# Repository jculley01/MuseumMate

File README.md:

# MuseumMate

## Executive Summary

MuseumMate is an advanced indoor navigation and exhibit interaction system, designed to enrich museum visits. Upon entering a museum, visitors receive a handheld device, the TourTag, which detects Ultra-wideband (UWB) signals from beacons placed throughout the premises. This device transmits signal strengths to a server to pinpoint the visitor's location, facilitating precise navigation through a user-friendly web application. Additionally, RFID tags on exhibits interact with the TourTags, allowing visitors to automatically access rich multimedia content about the exhibits they are near, thus enhancing their educational and interactive experience in the museum. This system seamlessly integrates efficient navigation with engaging exhibit exploration, revolutionizing the traditional museum visit.

## Context

MuseumMate utilizes a blend of Ultra-Wideband (UWB) and Radio Frequency Identification (RFID) technologies to streamline visitor flow and provide immersive educational content. The system's core components include:

### UWB Beacons (ESP32 UWB DW3000)
 
These beacons are utilized with trilateration to provide location accuracy within 10 centimeters , facilitating real-time, room-by-room navigation and helping to manage museum traffic by suggesting alternative routes to avoid congestion.

### RFID Tags

Attached to each exhibit, these tags work in tandem with TourTags—portable user devices that visitors carry. When a visitor approaches an exhibit, the TourTag scans the RFID tag to fetch multimedia content related to the exhibit.

### Server Technology

- Node.js with Express.js: Powers the backend infrastructure facilitating efficient data handling and communications.
- MinIO: A high-performance storage solution that manages the multimedia files which visitors access through their TourTags.
- InfluxDB: A time-series database optimized for storing and retrieving real-time metrics that help museum staff monitor and optimize visitor traffic patterns.

### TourTag Device

This custom-designed portable device features a compact PCB that includes all necessary hardware ports and connects to visitors' phones via a MagSafe-compatible enclosure, enhancing portability and ease of use.

## Special Features

- Advanced Navigation Algorithms: Utilizing Dijkstra's and the Traveling Salesman Problem (TSP) algorithms, MuseumMate provides optimized routing solutions that dynamically adjust to the visitor's location and crowd conditions, ensuring minimal wait times and balanced visitor distribution throughout the museum.
- RFID Multimedia Support: Each exhibit's RFID tag allows visitors to access a wide array of multimedia resources, such as audio descriptions, subtitled videos, and high-resolution images, enhancing the learning experience. This feature is particularly beneficial for visitors with physical impairments, as it supports 13 different languages, text-to-speech, and a ChatGPT AI Assistant.
- Real-Time Data Processing: With real-time analytics powered by InfluxDB, MuseumMate delivers instant insights to museum staff, enabling them to make informed decisions about exhibit openings and traffic management.
- Interactive Dashboard: A React-based web application that uses ApexCharts to visualize data from InfluxDB, providing staff with user-friendly interfaces to monitor museum operations effectively.
- Mobile Application: Developed using React Native, the mobile app is an integral part of the visitor experience, offering intuitive navigation, exhibit information, and easy access to personalized multimedia content.

## System Architecture

### Location Services Data Flow
In a museum, UWB (Ultra-Wideband) beacons are strategically positioned across various locations to ensure comprehensive coverage. These beacons constantly transmit signals that are picked up by a device known as the TourTag. This device collects a substantial number of signal readings, which are then sent to a Node.js server via UDP for processing. Upon receiving the data, the server updates the distance measurements from the corresponding beacons and employs trilateration with the three nearest beacons to compute the x,y coordinates of the TourTag. This location data is used to determine the specific room within the museum where the user is located. For visitors using the mobile app who wish to know their current location, the app queries a REST API endpoint. This endpoint responds with the room location based on the latest coordinates calculated for their TourTag. To facilitate efficient navigation through the museum, the server utilizes Dijkstra's algorithm for point-to-point routing and the Traveling Salesperson Problem (TSP) algorithm for routing through multiple nodes. The museum's layout is represented as a weighted adjacency graph, where the weights are calculated based on the Euclidean distances between rooms. Additionally, the graph dynamically adjusts by incorporating the current occupancy percentage of each room. This feature ensures that the routing suggestions can help visitors avoid crowded areas, thereby optimizing the flow of museum traffic and enhancing the visitor experience.

### Multimedia Data Flow

In the museum, each piece of artwork or exhibit is equipped with a unique RFID tag placed in its vicinity. Visitors interact with these RFID tags using their TourTag, a device that attaches to their smartphone via MagSafe. When a visitor taps their TourTag against an RFID tag, the action triggers the transmission of the RFID data to the Node.js server via UDP. This data includes the specific RFID that was tapped and identifies which TourTag was used. To notify the visitor's mobile app of the interaction, the server utilizes a WebSocket connection. This real-time communication channel informs the app about the specific RFID interaction triggered by the user. Following this notification, the mobile app makes a request to a REST API endpoint on the server. This API endpoint is responsible for retrieving multimedia content related to the RFID tag from MinIO, a high-performance object storage service. The server queries MinIO, obtains the multimedia files associated with the RFID, and generates URLs for these resources. It then sends these URLs back to the mobile app, allowing the app to display relevant multimedia content directly to the visitor. This seamless integration of RFID technology, mobile connectivity, and real-time data handling enhances the visitor's experience by providing instant access to rich multimedia content related to each exhibit they explore.

### Metrics/Data Transmission

InfluxDB, a specialized time series database, plays a crucial role in managing and storing all system metrics gathered from the hardware and the analytics data displayed on the dashboard. Each TourTag device communicates with the server via UDP, transmitting key information such as connection status, battery status, and battery level. The server processes and stores these metrics in InfluxDB. Additionally, the server captures and logs visitor data for dashboard insights, including room occupancy and duration of stay. These metrics are derived from internal server processes and subsequently stored in InfluxDB. Another important metric, exhibit ratings, is also stored in InfluxDB. Visitors can rate exhibits by scanning an RFID tag with their TourTag and submitting a 0-5 star review through a REST API endpoint, which the server then records in the database. This comprehensive data collection and storage system enables real-time monitoring and analytics to enhance visitor experience and operational efficiency.

## Quick Start Guide

### Prerequisites

- Node.js (v12.x or higher)
- npm (v6.x or higher)
- InfluxDB
- Minio (for object storage)
- Latest version of GoLang
- Gin Framework
- OpenAI Key
- Arduino IDE
- [ESP32 UWB DW3000](https://www.makerfabs.com/esp32-uwb-dw3000.html)
- RC522 RFID reader module
- [USB LiIon/LiPoly charger - v1.2](https://www.adafruit.com/product/259)
- LiIon Battery
- Eduroam network certification

### Hardware
1. Ensure you have the [Arduino environment set up](https://support.arduino.cc/hc/en-us/articles/360019833020-Download-and-install-Arduino-IDE) for ESP32 development.
2. [Install](https://docs.arduino.cc/software/ide-v1/tutorials/installing-libraries/) the dw3000 library to your Arduino environment.

#### Configure and Install MuseumMate Beacon

1. Connect your ESP32 UWB DW3000 to your computer.
2. Navigate to the `/MuseumMate_Beacon` directory.
3. Open `MuseumMate_Beacon.ino` in the IDE.
4. Modify `BEACON_ID` in line 36 to the correct value.
5. Adjust bytes 7 to 10 in `tx_resp_msg` in line 38 to match the `BEACON_ID`.
6. Build and flash the firmware to the ESP32 UWB DW3000 board and monitor the output.

#### Configure and Install MuseumMate TourTag

1. Navigate to the `/MuseumMate_TourTag` directory.
2. Open `common_definition.h` and modify `USERID` on line 5 to the correct value.
3. In `MuseumMateWifi.h`, update `SSID`, `EAP_ANONYMOUS_IDENTITY`, `EAP_IDENTITY`, `EAP_PASSWORD`, `EAP_USERNAME`, and `HOST` (server IP address) as necessary from lines 11 to 20.
4. In `MuseumMateWifi.cpp`, replace `test_root_ca` on line 11 with your institution's certificates if not on BU campus.
5. Build and flash `MuseumMate_TourTag.ino` to your ESP32 UWB DW3000 board, then monitor the serial output to confirm the firmware is running correctly.

### Node.js Server

Clone the repository to your local machine, download dependencies, and run on port 3000:

```bash
git clone https://github.com/jculley01/MuseumMate.git
cd MuseumMate
cd code
cd server
npm install
node index.js
```

### Mobile Application

1. **Clone the repository**:
   ```bash
   git clone (https://github.com/jculley01/MuseumMate)
   cd code
   cd front-end
   ```
2. **Install Dependencies**:
   ```bash
   npm install
   ```
3. **Start Development Server**
```bash
npx expo start
```
4. **Build Packages**
```bash
eas configure
eas build --platform ios
eas build -p android --profile preview
```

### ChatGPT Server

```bash
git clone https://github.com/jculley01/MuseumMate.git
cd MuseumMate
cd code
cd GPT
go mod tidy
go run main.go
```

### Administrator Dashboard
1. **Clone the repository:**
   ```bash
   git clone https://github.com/jculley01/MuseumMate.git
   cd code
   cd dashboard
   cd my-app
   ```
2. **Install Dependencies:**
   ```bash
   npm install
   ```
3. **Start the Application:**
   ```bash
   npm start
   ```

This will run the code in development mode. Open http://localhost:3001 to view in browser.

## System and Visitor Metrics in InfluxDB

### System Metrics

#### Connection Status
- **Measurement Name**: `connectionStatus`
- **Tags**:
  - `userID`: Identifies the user.
- **Fields**:
  - `online`: Binary value (1 for online, 0 for offline or asleep).
- **Context**: Captured via messages from the `connectionServer` to log the active connection status of user devices.

#### Battery Status
- **Measurement Name**: `batteryStatus`
- **Tags**:
  - `userID`: Identifies the user associated with the update.
- **Fields**:
  - `charging`: Indicates if the device is charging (1) or not (0).
  - `done`: Indicates if charging is complete (1) or not (0).
  - `status`: Describes the charging state (e.g., charging, not charging, charging done, error).
- **Context**: Logged upon receiving battery status updates via the `batteryStatusServer`.

#### Battery Level
- **Measurement Name**: `batteryLevel`
- **Tags**:
  - `userID`: Links to the specific user.
- **Fields**:
  - `level`: Represents the battery level as a percentage from 0 to 100.
- **Context**: Updates are received from the `batteryLevelServer` and monitored in real-time.

### Visitor Metrics

#### Room Access
- **Measurement Name**: `room_access`
- **Tags**:
  - `roomID`: Identifier for the accessed room.
- **Fields**:
  - `count`: Incremental counter, generally set to 1, to record accesses.
- **Context**: Logged during path calculations in the `/path/:userID` endpoint and during POST requests to `/tsp-path`.

#### Room Occupancy
- **Measurement Name**: `roomOccupancy`
- **Tags**:
  - `roomName`: Identifier for the room.
- **Fields**:
  - `count`: Current number of users in the room.
- **Context**: Periodically updated to reflect dynamic room occupancies based on user locations deduced from signal strength data.

#### Room Stay Duration
- **Measurement Name**: `roomStayDuration`
- **Tags**:
  - `userID`: Identifies the user.
  - `roomName`: Specifies the room.
- **Fields**:
  - `duration`: Time (in seconds) spent by the user in the room.
- **Context**: Recorded when users change rooms, as calculated by the `updateUserRoomDurations` function.

#### Exhibit Rating
- **Measurement Name**: `exhibitRating`
- **Tags**:
  - `exhibit`: Name of the exhibit being rated.
- **Fields**:
  - `rating`: Rating given by a user, scaled from 0 to 5.
- **Context**: Captured when a visitor rates an exhibit after scanning its RFID tag with their TourTag, sent via a REST API call to `/api/exhibit-rating`.

## API Endpoints

### General Information
GET /api/active-users: Returns the number of currently active users.
GET /api/total-users: Provides the total number of users within the last 24 hours.
GET /api/room-occupancies: Fetches the current occupancy of each room.
GET /api/exhibit-ratings: Retrieves ratings for each exhibit from the last year.
### Real-Time Tracking
GET /location/:userID: Returns the current location of a specific user.
GET /path/:userID: Provides the shortest path to a specified end node for a user.
POST /tsp-path: Calculates and returns the shortest path visiting specified nodes.
### Data Management
GET /rfid/:bucketName: Lists all objects within a specified bucket in Minio storage.

## Relevant Engineering Standards for MuseumMate System

### Electrical Design and Construction

#### IEEE 1547
- **Description**: This standard outlines requirements for the integration and interoperability of distributed energy resources with electrical power systems.
- **Impact**: Ensures that electrical components like TourTag and Beacon devices meet safety and performance criteria when connected to the electrical grid.

#### National Electrical Safety Code (NESC)
- **Description**: Provides guidelines for the safe installation, operation, and maintenance of electrical power and communication utilities.
- **Impact**: Guarantees the safety of MuseumMate's electrical components for both end-users and service personnel.

### Software Design and Coding Standards

#### MISRA C
- **Description**: Compliance with MISRA C guidelines ensures the reliability, maintainability, and portability of the C code used in embedded systems.
- **Impact**: Critical for developing the firmware for TourTag and Beacon devices.

#### React Native Framework
- **Description**: Adherence to best practices in React Native for building the app.
- **Impact**: Optimizes performance and compatibility across Android and iOS platforms.

#### Expo Managed Workflow
- **Description**: Uses the managed workflow by Expo, which simplifies much of the app configuration.
- **Impact**: Lowers the barrier to entry for developers and ensures the use of industry-standard approaches.

### Communication and Internet Protocols

#### IEEE 802.11
- **Description**: Standards for wireless local area network (WLAN) communications.
- **Impact**: Essential for the WiFi communication of TourTag devices, ensuring compatibility and security.

#### ISO/IEC 14443
- **Description**: Standard for short-range wireless connectivity, used in contactless systems.
- **Impact**: Key for identification and access control.

#### ISO/IEC 24730-5
- **Description**: Addresses real-time locating systems (RTLS) using Ultra-Wideband (UWB) technology.
- **Impact**: Emphasizes interoperability and compatibility across devices.

#### IEEE 802.15.4z-2020
- **Description**: Enhanced UWB Physical Layers (PHYs) and ranging techniques.
- **Impact**: Crucial for precise indoor positioning and communication in low-rate wireless networks.

#### WebSockets for Real-Time Communication
- **Description**: Enables efficient real-time data communication with minimal overhead and latency.

#### HTTPS/TLS 1.3
- **Description**: Ensures the latest security standards for transmitting data securely over the Internet.
- **Impact**: Protects user data from interception and tampering.

### Operational Environment and Governmental Requirements

#### IEC 61131-3
- **Description**: Defines programming languages for PLCs in industrial settings.
- **Impact**: Ensures adherence to industrial best practices for safety and reliability.

#### ISO/IEC 18305
- **Description**: Methodology for testing and evaluating indoor positioning systems.
- **Impact**: Guarantees performance and reliability in operational environments.

#### FCC Regulations
- **Description**: Federal Communications Commission regulations for devices emitting radio frequencies.
- **Impact**: Prevents interference and ensures compliance with exposure limits.

### API and Integration Standards

#### RESTful API Conventions
- **Description**: Best practices for API design.
- **Impact**: Ensures effective communication with back-end services in a stateless, cacheable, and uniform manner.

#### JSON:API Specification for APIs
- **Description**: Standard for building APIs in JSON.
- **Impact**: Simplifies code, enhances efficiency, and facilitates better server-client interactions.

### User Interface and Accessibility

#### Material Design and Human Interface Guidelines
- **Description**: Design guidelines for Android (Material Design) and iOS (Human Interface Guidelines).
- **Impact**: Improves user experience and interface intuitiveness, ensuring a native look and feel on each platform.
## Demo Links
- https://drive.google.com/file/d/1xxcSSfVXUqi0H7ppWGPCUCPkb2fy99GB/view?usp=drive_link
- https://drive.google.com/file/d/10ySGV_i79_dgyBcs_XPV-sKXKdbrn-Mb/view?usp=drive_link

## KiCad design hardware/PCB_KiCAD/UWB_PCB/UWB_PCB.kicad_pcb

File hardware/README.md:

# MuseumMate Hardware

This directory contains all hardware component files for the MuseumMate project, including PCB designs and enclosure models for the TourTag device and Beacon. These files are crucial for the manufacturing and assembly of the hardware components.

## Directory Structure

- `/PCB_KiCAD`: Contains all KiCAD files for the PCB design of the TourTag.
- `/Enclosures`: Includes the CAD files for the enclosures of both the TourTag and Beacon.

## PCB Design for TourTag

### Schematic Diagram

The schematic diagram provides a detailed visual representation of the electrical connections and components within the TourTag device, crucial for circuit design and troubleshooting.

- **TourTag Device Schematic**: This schematic displays the circuit design, detailing all integrated circuits, their connections, and header pins for modular component attachment.

- **Links to TourTag Device Schematic**:
  - [TourTag Device Schematic (PDF)](/media/pcbschematic.pdf)
  - [Schematic Source Files (KiCAD_SCH)](/hardware/PCB_KiCAD/UWB_PCB/UWB_PCB.kicad_sch)
  - **Note**: Ensure you have the necessary software to open CAD and PCB design files, such as KiCAD or a compatible viewer.

### PCB Layout

This section shows the arrangement of components on the TourTag circuit board, essential for manufacturing and assembly guidance.

- **TourTag Devices PCB**: A detailed layout showing the placement of components, traces, vias, and header connectors.

- **Links to TourTag Devices PCB Layout**:
  - [TourTag Devices PCB Layout (PDF)](/media/pcbdesign.pdf)
  - [Editable PCB Design File (KiCAD_PCB)](/hardware/PCB_KiCAD/UWB_PCB/UWB_PCB.kicad_pcb)
  - **Note**: Ensure you have the necessary software to open CAD and PCB design files, such as KiCAD or a compatible viewer.

## Enclosure Designs

### Beacon Enclosure

Similarly, the enclosure for the Beacon ensures it is safeguarded against environmental factors and blends seamlessly within its deployment setting.

- **Design Overview**: The beacon enclosure also has three holes in it. The first hole on the bottom of the enclosure is for the ultra-wideband antenna. This allows the antenna to have nothing in its way to make the most accurate location tracking. The hole on the left side of the enclosure is for the charger. The hole on the top of the enclosure is so we can put the UWB in the enclosure. Also, the MuseamMate holes allow for heat dissipation. 

- **Manufacturing and Assembly**:Like the TourTag enclosure, there were two materials that were taken into consideration when making the enclosure. The main two factors in deciding on a material were weight and cost. We decided that ABS was the right material for this because it can handle more heat just in case the UWB gets warm.

- **Links to Beacon Enclosure Design**:
  - [Beacon Enclosure Design (OnShape)](https://cad.onshape.com/documents/9a545c80bb0287f4124073f7/w/fd1997773b928c532072d26f/e/a766d1128aeb9f154a371a63)
  - [Beacon Enclosure Source File (STL)](./Enclosures/UWBbeaconsenclosure.stl)
  - **Note**: Ensure you have the necessary software to view and edit the design files, such as OnShape or other CAD software.

### TourTag Enclosure

The enclosure for the TourTag is designed to protect the device while maintaining functionality and accessibility for maintenance and upgrades.

- **Design Overview**: 
The TourTag enclosure encloses the PCB, the RFID, the ultra-wideband ESP, the battery monitor and the battery. The Enclosure is designed to be attached to the back of the user's phone using MagSafe. Each enclosure will have a Magsafe Magnet inside ensuring a seamless experience for the user. On the Enclosure, there will also be three holes. The hole on the right side of the enclosure will be for the ultra-wideband antenna. This ensures that the beacons can accurately detect where the user is in the museum. The hole on the left side of the enclosure will allow the museum to charge the enclosure without taking the PBC out of the enclosure. Finally, the hole on the top of the enclosure will allow the museum to take the electronic components out of the enclosure is needed. 

- **Manufacturing and Assembly**: There were two materials that were taken into consideration when making the enclosure. The main two factors in deciding on a material were weight and cost. First off, the enclosure had to be light because it was going to be put on the back of the phone. If the enclosure was too heavy, the enclosure would fall off the phone making the user experience bad. Secondly, the enclosure has to be inexpensive. This is because the museum has to make as many enclosures as there are users in a museum. If the enclosure were expensive it would cost the museum a lot of money making them not want to use MuseumMate. The two materials considered were PLA and ABS. After weighing the pros and cons of each material like how brittle the material is and the heat tolerance, we went with PLA because it is not as brittle as ABS and if the public is using the enclosures, we want the enclosures to hold up to wear and tear. To manufacture the enclosures, we 3D printed them. This is because they are easy to manufacture yet strong.

- **Links to TourTag Enclosure Design**:
  - [TourTag Enclosure Design (Onshape)](https://cad.onshape.com/documents/7aaab9504794f084db368c22/w/5395925245216489e8e7f16a/e/d80cc8f357e229253dcfb44c)
  - [TourTag Enclosure Source File (STL)](./Enclosures/Tourtagenclosure.stl)
  - **Note**: Ensure you have the necessary software to view and edit the design files, such as OnShape or other CAD software.

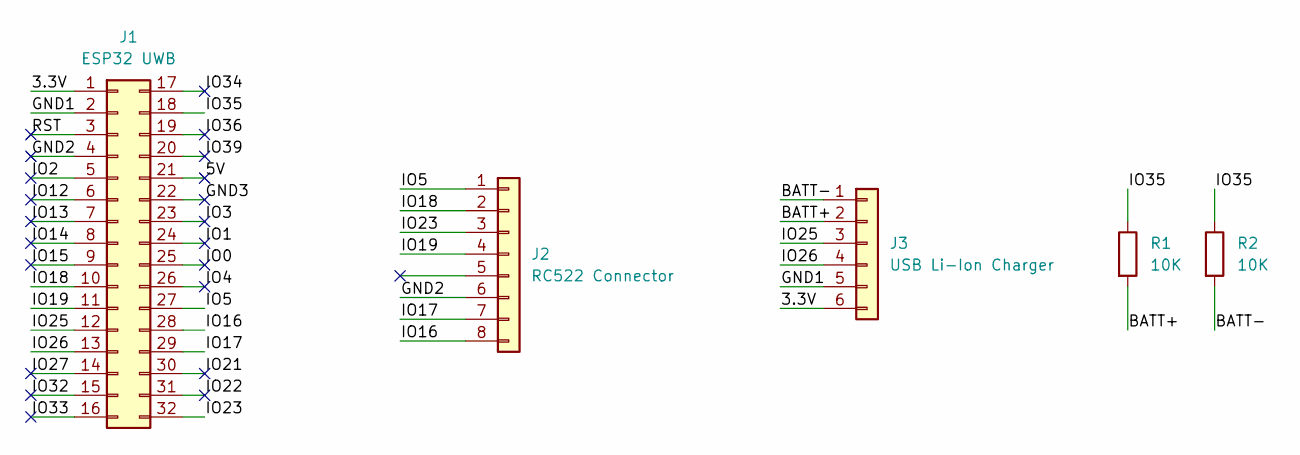
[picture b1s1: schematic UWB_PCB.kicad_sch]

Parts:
J1: ESP32 UWB; ESP_UWB_Final
J2: RC522 Connector; RC522_Module
J3: USB Li-Ion Charger; Li-Ion_Charger
R1, R2: 10K; R_1206_3216Metric

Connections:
/3.3V: J1.1, J3.6
/5V: J1.21
/BATT+: J3.2, R1.2
/BATT-: J3.1, R2.2
/GND1: J1.2, J3.5
/GND2: J1.4, J2.6
/GND3: J1.22
/IO0: J1.25
/IO1: J1.24
/IO2: J1.5
/IO3: J1.23
/IO4: J1.26
/IO5: J1.27, J2.1
/IO12: J1.6
/IO13: J1.7
/IO14: J1.8
/IO15: J1.9
/IO16: J1.28, J2.8
/IO17: J1.29, J2.7
/IO18: J1.10, J2.2
/IO19: J1.11, J2.4
/IO21: J1.30
/IO22: J1.31
/IO23: J1.32, J2.3
/IO25: J1.12, J3.3
/IO26: J1.13, J3.4
/IO27: J1.14
/IO32: J1.15
/IO33: J1.16
/IO34: J1.17
/IO35: J1.18, R1.1, R2.1
/IO36: J1.19
/IO39: J1.20
/RST: J1.3

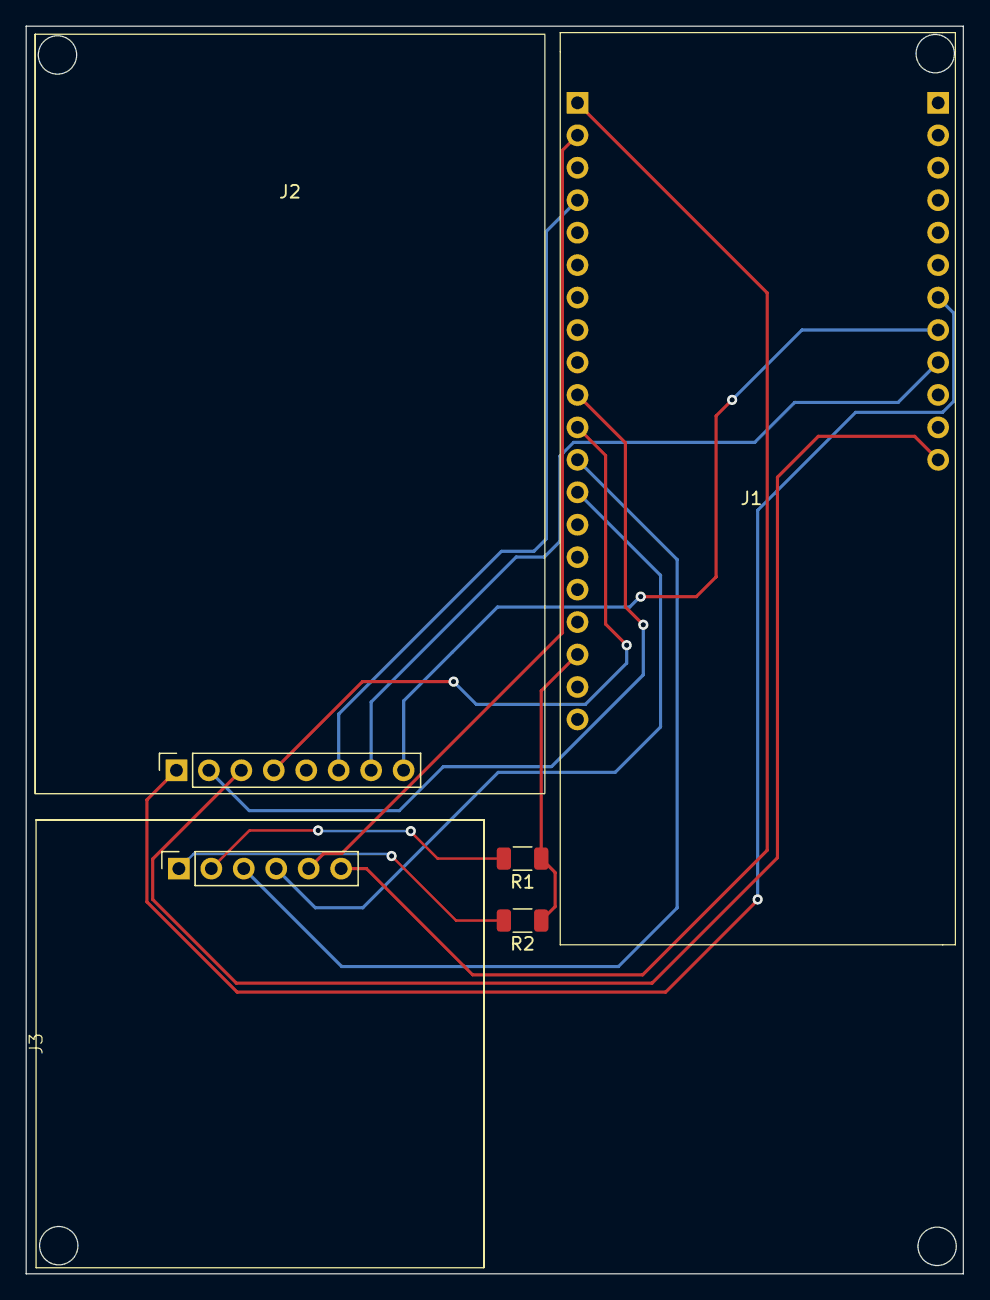
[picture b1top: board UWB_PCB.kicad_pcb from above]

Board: 2 copper layers, 73.4 x 97.7 mm, 5 parts (0 on the bottom side), 14 nets.

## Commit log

2023-10-24 Create test
2023-10-24 Update files
2023-10-26 Front end
2023-11-03 KNN implementation
    This update includes KNN location service with test data.
2023-11-07 Upload RFID
2023-11-09 maps
2023-11-09 updated code
2023-11-10 updated files
2023-11-15 Current Location
2023-12-04 implemented RFID
2023-12-04 added readme
2023-12-04 Current location
    Currently not sending to endpoint, needs styling
2023-12-05 Remove RFID
2023-12-05 upload hardware code
2023-12-05 updated RFID
2023-12-05 update buckets
2023-12-08 RFID
2024-01-22 ratings
    rating system, needs to be tested with RFIDs
2024-01-31 working prototype
2024-01-31 TTS and translation
2024-02-01 API GPT w fe integration
2024-02-01 uwb
    implemented uwb functions
2024-02-08 uwb finalized
    This is the code with tested uwb implementation
2024-02-15 pushed kicad hardware files
2024-02-16 updated pcb
2024-02-17 PCB changes
2024-02-23 Dashboard unstyled
2024-02-25 PCB updates
2024-02-26 dash
2024-02-26 included data stream to InfluxDB
2024-02-27 adjusted logic
2024-02-28 exhibit overview card styled correctly
2024-02-28 touched up on minor styling for exhibit overview
2024-02-28 semi aligned landing page with mock data
2024-02-28 slight style changes
2024-02-28 updated styling
2024-02-28 slight fixes to node graph
2024-02-28 Dashboard and App Updates
2024-02-29 Screen Navigation
2024-03-01 slight udp changes
2024-03-01 implemented machine learning
2024-03-11 Dashboard room overview
2024-03-19 Dashboard styling
2024-03-19 updated dynamic pooling
2024-03-27 New UWB Device Code
2024-03-28 rating, DDNS, dashboard
2024-03-30 pcb iteration 3
2024-04-01 Notification and Rating
2024-04-02 added performance logging
    added performance logging
2024-04-02 Revert "added performance logging"
    This reverts commit 061ecb4bb2ff049554bb90018605ef6b42c65b87.
2024-04-02 Revert "Revert "added performance logging""
    This reverts commit bf22378e9a1b4b2354c0600261e34e6de4b3ef5c.
2024-04-02 stashed
2024-04-02 server cors, test file
2024-04-04 pushed performance data
    asf
2024-04-07 added rating api endpoint
2024-04-07 added congestion and implemented battery procedures for hardware
2024-04-08 server push
2024-04-08 server
2024-04-08 Server with congestion and 9 floor beacons
2024-04-09 App Updates
2024-04-09 App dev
2024-04-17 added apis for influxDB retrievals
2024-04-24 fixed apis and dashboard
2024-04-24 fixed top menu bar
2024-04-24 Dashboard pages and app
2024-04-24 dashboard work
2024-04-24 completed dashboard
2024-04-24 read me
2024-04-24 main read me
2024-04-28 Upload BLE Hardware README
2024-04-28 Create UWB README
2024-04-28 hardware documentation
2024-04-28 Upload Previous Reports
2024-04-28 app working ios
2024-04-28 Finished readmes
2024-04-28 here
2024-04-28 updated readmes
2024-04-28 Rename Users Manual 04-15-2024.pdf to 2024-04-15 Users Manual.pdf
2024-04-30 server fixes
2024-05-02 rating refresh
